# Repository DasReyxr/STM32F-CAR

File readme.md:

# Carrito Seguidor de Línea con Lógica Difusa

Este proyecto presenta un **carrito autónomo seguidor de línea** basado en un microcontrolador STM32 y un sistema de control por **lógica difusa (Fuzzy Logic)**. El objetivo es detectar la posición de la línea y ajustar la velocidad de los motores para mantener el seguimiento de manera estable y eficiente.

## ✨ Características principales
- Seguimiento automático de línea mediante sensores infrarrojos.
- Control adaptativo mediante lógica difusa.
- Implementación sobre plataforma STM32.
- Diseño orientado a demostración, pruebas y desarrollo académico.

## 🧠 ¿Cómo funciona?
El sistema lee la señal de los sensores, identifica si el carrito está ligeramente a la izquierda, a la derecha o sobre la línea, y genera una respuesta para corregir el movimiento de los motores, manteniéndose sobre la trayectoria.

## 🛠️ Diseño del sistema

El sistema sigue una secuencia clara de procesamiento:

1. **Adquisición de datos**: se toman las lecturas de los dos sensores.
2. **Difuminación de entradas**: los valores obtenidos se difuminan para representar el grado de pertenencia a las variables difusas.
3. **Reglas de Mamdani**: se aplican las reglas difusas para evaluar la acción de control.
4. **Defuzzificación por centroide**: se obtiene un valor numérico que indica la corrección necesaria.
5. **Actuación sobre los motores**: el resultado se envía al puente H para controlar el movimiento del carrito.

```mermaid
flowchart LR
    A[Sensor izquierdo] --> B[Lecturas de entrada]
    C[Sensor derecho] --> B
    B --> D[Difusificación]
    D --> E[Reglas de Mamdani]
    E --> F[Centroide]
    F --> G[Control de motores]
    G --> H[Motor izquierdo]
    G --> I[Motor derecho]
```

### Componentes principales
- **Microcontrolador:** BlackPill STM32F411CEU
- **Sensores:** QTR-8A
- **Puente H:** TB6612FNG
- **Control:** lógica difusa basada en reglas de Mamdani
- **Actuadores:** motores DC
- **Fuente de alimentación:** batería o fuente adecuada para el sistema

## 📷 Imagen del prototipo

A continuación se muestra una vista del prototipo desarrollado para el carrito seguidor de línea:

## 🎥 Demo
Aquí puedes ver una demostración del funcionamiento del carrito:

https://github.com/user-attachments/assets/0d9d8957-ae0a-4fae-b08e-12143651e8d6

## 👥 Equipo
- Roberto López - [Roberto](https://github.com/Roberto-dot)
- Kevin Lara - [Gyonyu](https://github.com/Gyonyu)
- Das Reyes - [Das](https://github.com/DasReyxr)

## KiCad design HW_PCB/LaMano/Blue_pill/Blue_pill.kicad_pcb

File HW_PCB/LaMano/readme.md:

# Log File
## 6-29-26

## 6-29-26

## 6-29-26

## 6-24-26

## 6-23-26

# 8-27-26

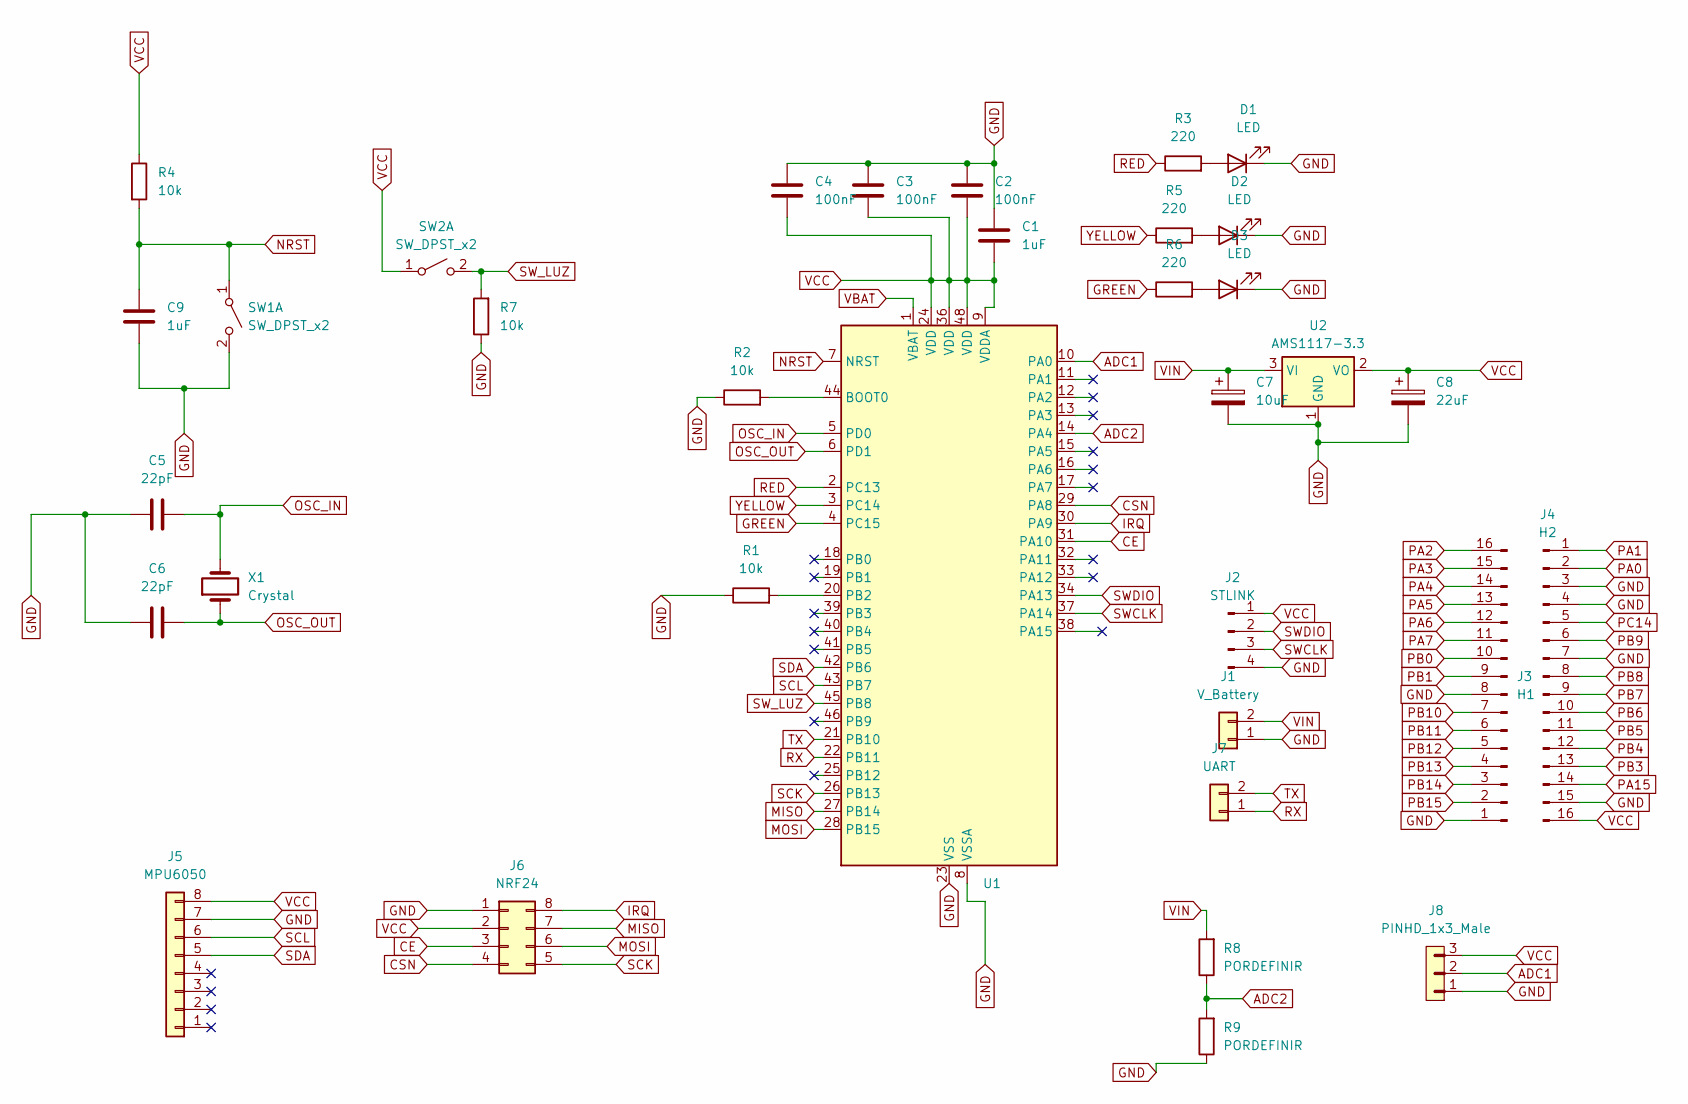
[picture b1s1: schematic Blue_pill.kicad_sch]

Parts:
C1, C9: 1uF; C_0805_2012Metric_Pad1.18x1.45mm_HandSolder
C2, C3, C4: 100nF; C_0805_2012Metric_Pad1.18x1.45mm_HandSolder
C5, C6: 22pF; C_0805_2012Metric_Pad1.18x1.45mm_HandSolder
C7: 10uF; C_0805_2012Metric_Pad1.18x1.45mm_HandSolder
C8: 22uF; C_0805_2012Metric_Pad1.18x1.45mm_HandSolder
D1, D2, D3: LED; LED_0805_2012Metric
J1: V_Battery; PinHeader_1x02_P2.54mm_Vertical
J2: STLINK; PinHeader_1x04_P2.54mm_Vertical
J3: H1; PinHeader_1x16_P2.54mm_Vertical
J4: H2; PinHeader_1x16_P2.54mm_Vertical
J5: MPU6050; PinHeader_1x08_P2.54mm_Vertical
J6: NRF24; PinHeader_2x04_P2.54mm_Vertical
J7: UART; PinHeader_1x02_P2.54mm_Vertical
J8: PINHD_1x3_Male; PinHeader_1x03_P2.54mm_Vertical
R1, R2, R4, R7: 10k; R_0805_2012Metric
R3, R5, R6: 220; R_0805_2012Metric
R8, R9: PORDEFINIR; R_0805_2012Metric
SW1: SW_DPST_x2; SWESPECIAL
SW2: SW_DPST_x2; PinHeader_1x02_P2.54mm_Vertical
U1: STM32F103C8Tx; LQFP-48_7x7mm_P0.5mm
U2: AMS1117-3.3; SOT-223-3_TabPin2
X1: Crystal; XTAL_NX5032GA-8.000M-STD-CSU-1

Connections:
ADC1: J8.2, U1.10 (PA0)
ADC2: R8.1, R9.2, U1.14 (PA4)
CE: J6.3, U1.31 (PA10)
CSN: J6.4, U1.29 (PA8)
GND: C1.2, C2.2, C3.2, C4.2, C5.2, C6.2, C7.2, C8.2, C9.1, D1.1 (K), D2.1 (K), D3.1 (K), J1.1, J2.4, J3.1, J3.8, J4.3, J4.4, J4.7, J4.15, J5.7, J6.1, J8.1, R1.1, R2.1, R7.1, R9.1, SW1.2 (B), U1.8 (VSSA), U1.23 (VSS), U1.35 (VSS), U1.47 (VSS), U2.1 (GND)
GREEN: R6.1, U1.4 (PC15)
IRQ: J6.8, U1.30 (PA9)
MISO: J6.7, U1.27 (PB14)
MOSI: J6.6, U1.28 (PB15)
NRST: C9.2, R4.2, SW1.1 (A), U1.7 (NRST)
unnamed: D1.2 (A), R3.2
unnamed: D2.2 (A), R5.2
unnamed: D3.2 (A), R6.2
unnamed: R2.2, U1.44 (BOOT0)
unnamed: R1.2, U1.20 (PB2)
OSC_IN: C5.1, U1.5 (PD0), X1.2
OSC_OUT: C6.1, U1.6 (PD1), X1.1
RED: R3.1, U1.2 (PC13)
RX: J7.1, U1.22 (PB11)
SCK: J6.5, U1.26 (PB13)
SCL: J5.6, U1.43 (PB7)
SDA: J5.5, U1.42 (PB6)
SWCLK: J2.3, U1.37 (PA14)
SWDIO: J2.2, U1.34 (PA13)
SW_LUZ: R7.2, SW2.2 (B), U1.45 (PB8)
TX: J7.2, U1.21 (PB10)
VBAT: U1.1 (VBAT)
VCC: C1.1, C2.1, C3.1, C4.1, C8.1, J2.1, J4.16, J5.8, J6.2, J8.3, R4.1, SW2.1 (A), U1.9 (VDDA), U1.24 (VDD), U1.36 (VDD), U1.48 (VDD), U2.2 (VO)
VIN: C7.1, J1.2, R8.2, U2.3 (VI)
YELLOW: R5.1, U1.3 (PC14)

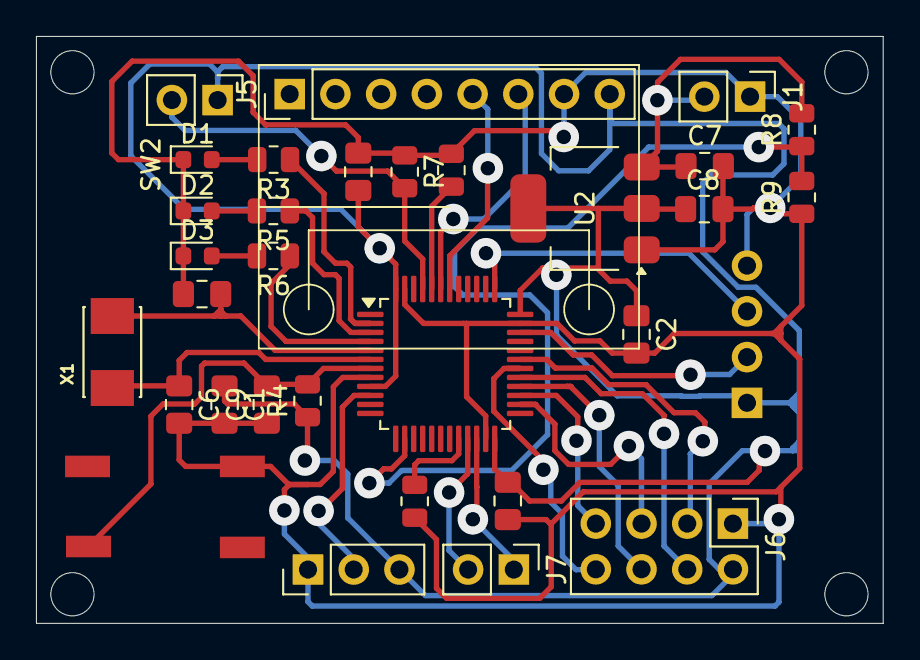
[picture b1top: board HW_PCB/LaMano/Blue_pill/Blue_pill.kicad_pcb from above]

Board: 2 copper layers, 47.0 x 32.6 mm, 32 parts (1 on the bottom side), 29 nets.

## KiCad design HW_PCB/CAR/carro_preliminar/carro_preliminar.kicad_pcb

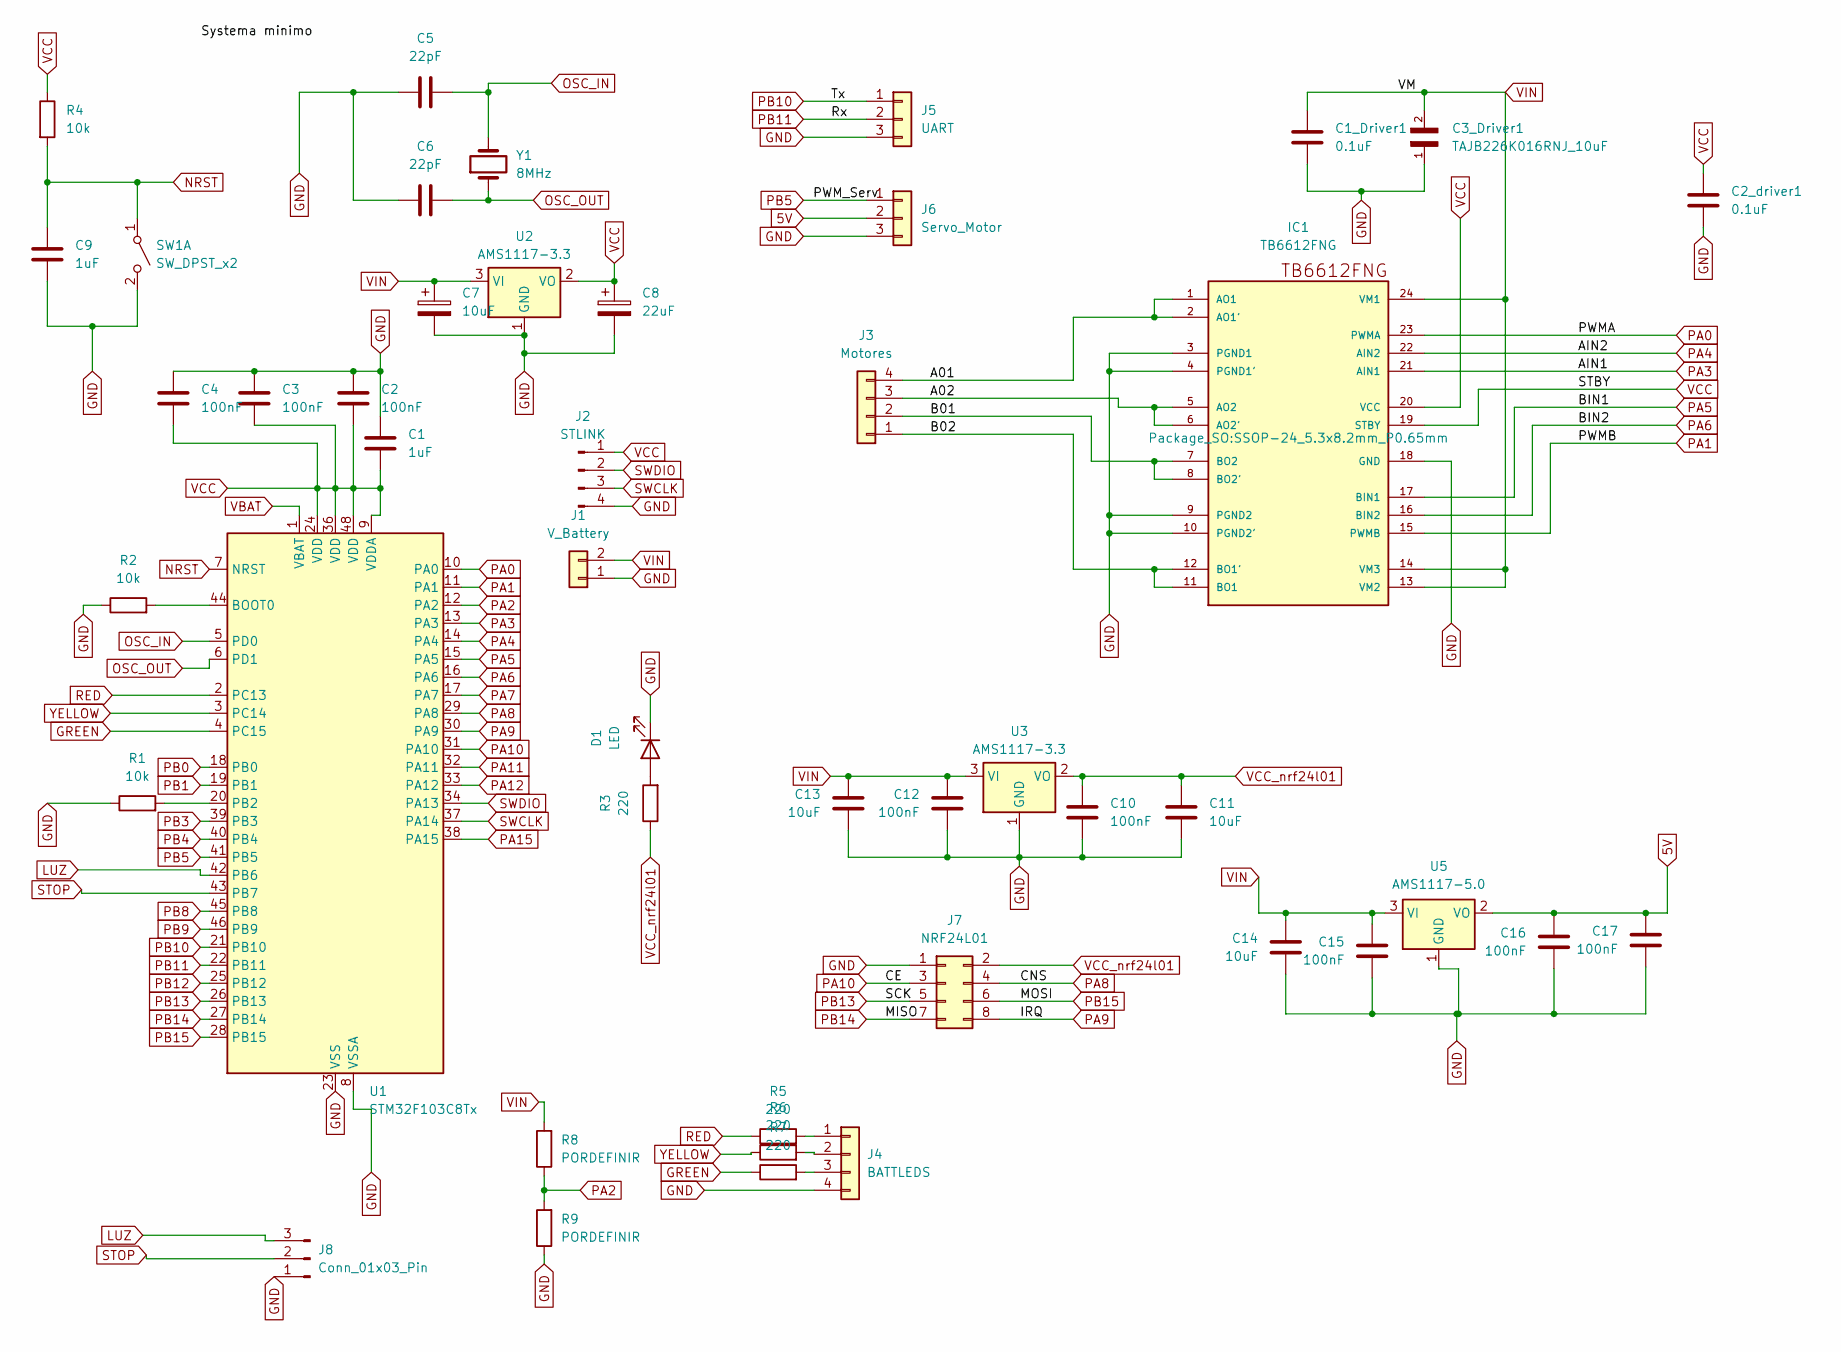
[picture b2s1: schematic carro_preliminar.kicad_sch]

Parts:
C1: 1uF; C_0805_2012Metric
C1_Driver1, C2_driver1: 0.1uF; C_0805_2012Metric
C2, C3, C4, C10, C12, C15, C16, C17: 100nF; C_0805_2012Metric_Pad1.18x1.45mm_HandSolder
C3_Driver1: TAJB226K016RNJ_10uF; CAPPC3528X210N; DigiKey_Part_Number 478-1682-1-ND
C5, C6: 22pF; C_0805_2012Metric_Pad1.18x1.45mm_HandSolder
C7, C11, C13, C14: 10uF; C_0805_2012Metric_Pad1.18x1.45mm_HandSolder
C8: 22uF; C_0805_2012Metric_Pad1.18x1.45mm_HandSolder
C9: 1uF; C_0805_2012Metric_Pad1.18x1.45mm_HandSolder
D1: LED; LED_0603_1608Metric
IC1: TB6612FNG; SSOP-24_5.3x8.2mm_P0.65mm
J1: V_Battery; PinHeader_1x02_P2.54mm_Vertical
J2: STLINK; PinHeader_1x04_P2.54mm_Vertical
J3: Motores; PinHeader_1x04_P2.54mm_Vertical
J4: BATTLEDS; PinHeader_1x04_P2.54mm_Vertical
J5: UART; PinHeader_1x03_P2.54mm_Vertical
J6: Servo_Motor; PinHeader_1x03_P2.54mm_Vertical
J7: NRF24L01; PinHeader_2x04_P2.54mm_Vertical
J8: Conn_01x03_Pin; PinHeader_1x03_P2.54mm_Vertical
R1, R2, R4: 10k; R_0805_2012Metric
R3, R5, R6, R7: 220; R_0805_2012Metric
R8, R9: PORDEFINIR; R_0805_2012Metric
SW1: SW_DPST_x2; Untitled
U1: STM32F103C8Tx; LQFP-48_7x7mm_P0.5mm
U2, U3: AMS1117-3.3; SOT-223-3_TabPin2
U5: AMS1117-5.0; SOT-223-3_TabPin2
Y1: 8MHz; XTAL_NX5032GA-8.000M-STD-CSU-1

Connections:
5V: C16.1, C17.1, J6.2, U5.2 (VO)
/A01: IC1.1 (AO1), IC1.2 (AO1'), J3.4
/A02: IC1.5 (AO2), IC1.6 (AO2'), J3.3
/B01: IC1.7 (BO2), IC1.8 (BO2'), J3.2
/B02: IC1.11 (BO1), IC1.12 (BO1'), J3.1
GND: C1.2, C1_Driver1.2, C2.2, C2_driver1.2, C3.2, C3_Driver1.1, C4.2, C5.2, C6.2, C7.2, C8.2, C9.1, C10.2, C11.2, C12.2, C13.2, C14.2, C15.2, C16.2, C17.2, D1.1 (K), IC1.3 (PGND1), IC1.4 (PGND1'), IC1.9 (PGND2), IC1.10 (PGND2'), IC1.18 (GND), J1.1, J2.4, J4.4, J5.3, J6.3, J7.1, J8.1, R1.1, R2.1, R9.1, SW1.2 (B), U1.8 (VSSA), U1.23 (VSS), U1.35 (VSS), U1.47 (VSS), U2.1 (GND), U3.1 (GND), U5.1 (GND)
GREEN: R7.1, U1.4 (PC15)
LUZ: J8.3, U1.42 (PB6)
NRST: C9.2, R4.2, SW1.1 (A), U1.7 (NRST)
unnamed: D1.2 (A), R3.2
unnamed: J4.1, R5.2
unnamed: J4.2, R6.2
unnamed: J4.3, R7.2
unnamed: R2.2, U1.44 (BOOT0)
unnamed: R1.2, U1.20 (PB2)
OSC_IN: C5.1, U1.5 (PD0), Y1.2
OSC_OUT: C6.1, U1.6 (PD1), Y1.1
PA0: IC1.23 (PWMA), U1.10 (PA0)
PA1: IC1.15 (PWMB), U1.11 (PA1)
PA2: R8.1, R9.2, U1.12 (PA2)
PA3: IC1.21 (AIN1), U1.13 (PA3)
PA4: IC1.22 (AIN2), U1.14 (PA4)
PA5: IC1.17 (BIN1), U1.15 (PA5)
PA6: IC1.16 (BIN2), U1.16 (PA6)
PA7: U1.17 (PA7)
PA8: J7.4, U1.29 (PA8)
PA9: J7.8, U1.30 (PA9)
PA10: J7.3, U1.31 (PA10)
PA11: U1.32 (PA11)
PA12: U1.33 (PA12)
PA15: U1.38 (PA15)
PB0: U1.18 (PB0)
PB1: U1.19 (PB1)
PB3: U1.39 (PB3)
PB4: U1.40 (PB4)
PB5: J6.1, U1.41 (PB5)
PB8: U1.45 (PB8)
PB9: U1.46 (PB9)
PB10: J5.1, U1.21 (PB10)
PB11: J5.2, U1.22 (PB11)
PB12: U1.25 (PB12)
PB13: J7.5, U1.26 (PB13)
PB14: J7.7, U1.27 (PB14)
PB15: J7.6, U1.28 (PB15)
RED: R5.1, U1.2 (PC13)
STOP: J8.2, U1.43 (PB7)
SWCLK: J2.3, U1.37 (PA14)
SWDIO: J2.2, U1.34 (PA13)
VBAT: U1.1 (VBAT)
VCC: C1.1, C2.1, C2_driver1.1, C3.1, C4.1, C8.1, IC1.19 (STBY), IC1.20 (VCC), J2.1, R4.1, U1.9 (VDDA), U1.24 (VDD), U1.36 (VDD), U1.48 (VDD), U2.2 (VO)
VCC_nrf24l01: C10.1, C11.1, J7.2, R3.1, U3.2 (VO)
VIN: C1_Driver1.1, C3_Driver1.2, C7.1, C12.1, C13.1, C14.1, C15.1, IC1.13 (VM2), IC1.14 (VM3), IC1.24 (VM1), J1.2, R8.2, U2.3 (VI), U3.3 (VI), U5.3 (VI)
YELLOW: R6.1, U1.3 (PC14)

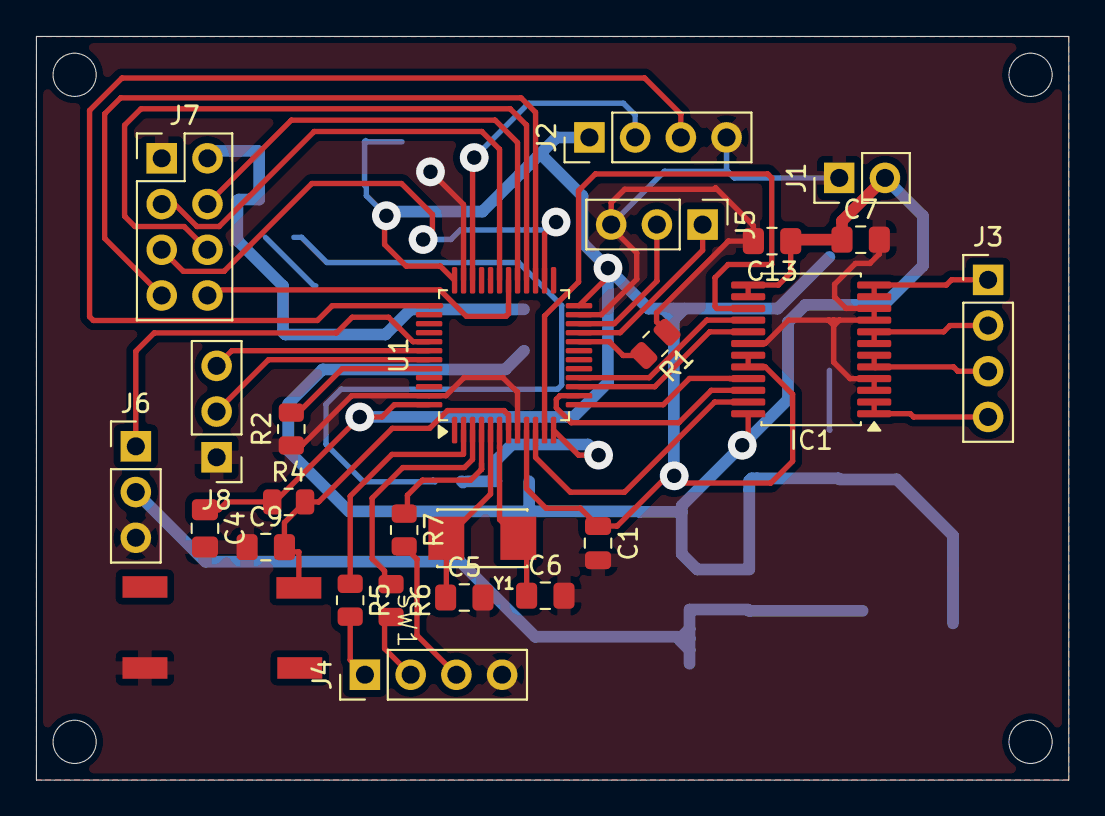
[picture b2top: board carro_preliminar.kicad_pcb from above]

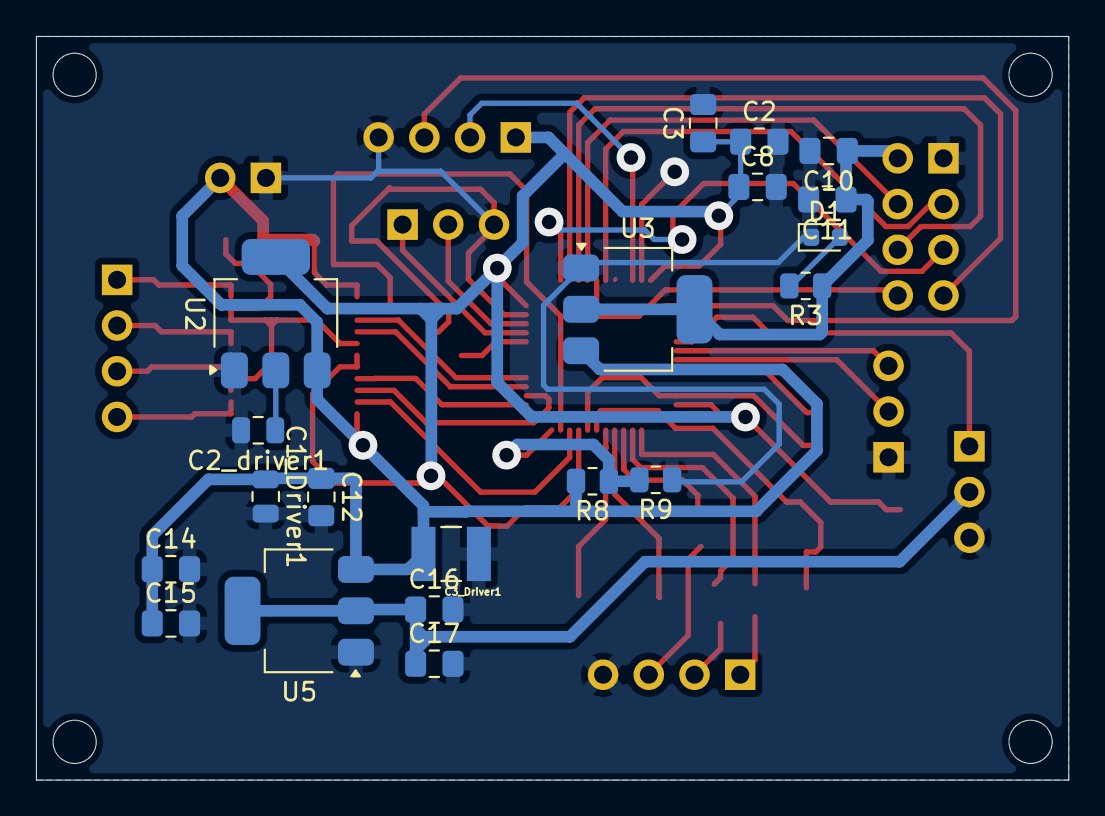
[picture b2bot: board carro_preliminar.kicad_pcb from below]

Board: 2 copper layers, 57.4 x 41.3 mm, 45 parts (20 on the bottom side), 41 nets.

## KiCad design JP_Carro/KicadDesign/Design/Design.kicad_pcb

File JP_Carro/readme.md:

# Carrito Seguidor de Línea con Lógica Difusa

Este proyecto presenta un **carrito autónomo seguidor de línea** basado en un microcontrolador STM32 y un sistema de control por **lógica difusa (Fuzzy Logic)**. El objetivo es detectar la posición de la línea y ajustar la velocidad de los motores para mantener el seguimiento de forma estable y eficiente.

## ✨ Características principales
- Seguimiento automático de línea mediante sensores infrarrojos.
- Control adaptativo usando lógica difusa.
- Implementación sobre plataforma STM32.
- Diseño orientado a demostración, pruebas y desarrollo académico.

## 🧠 ¿Cómo funciona?
El sistema lee la señal de los sensores, identifica si el robot está ligeramente a la izquierda, derecha o sobre la línea, y genera una respuesta para corregir el movimiento de los motores.

## 🛠️ Diseño del sistema

El sistema se basa en una secuencia clara de procesamiento:

1. **Adquisición de datos**: se toman las lecturas de los dos sensores.
2. **Difusión de entradas**: los valores obtenidos se difuminan para representar el grado de pertenencia a las variables difusas.
3. **Reglas de Mamdani**: se aplican las reglas difusas para evaluar la acción de control.
4. **Defuzzificación por centroide**: se obtiene un valor numérico que indica la corrección necesaria.
5. **Actuación sobre los motores**: el resultado se envía al puente H para controlar el movimiento del carrito.

```mermaid
flowchart LR
    A[Sensor izquierdo] --> B[Lecturas de entrada]
    C[Sensor derecho] --> B
    B --> D[Difusificación]
    D --> E[Reglas de Mamdani]
    E --> F[Centroide]
    F --> G[Control de motores]
    G --> H[Motor izquierdo]
    G --> I[Motor derecho]
```

### Componentes principales
- **Microcontrolador:** BlackPill STM32F411CEU
- **Sensores:** QTR-8A
- **Puente H:** TB6612FNG
- **Control:** lógica difusa basada en reglas de Mamdani
- **Actuadores:** motores DC
- **Fuente de alimentación:** batería o fuente adecuada para el sistema

## 📷 Imagen del prototipo

A continuación se muestra una vista del prototipo desarrollado para el carrito seguidor de línea:

## 🎥 Demo
Aquí puedes ver una demostración del funcionamiento del carrito:

https://github.com/user-attachments/assets/0d9d8957-ae0a-4fae-b08e-12143651e8d6

## 👥 Equipo
- Roberto López - [Roberto](https://github.com/Roberto-dot)
- Kevin Lara - [Gyonyu](https://github.com/Gyonyu)
- Das Reyes - [Das](https://github.com/DasReyxr)

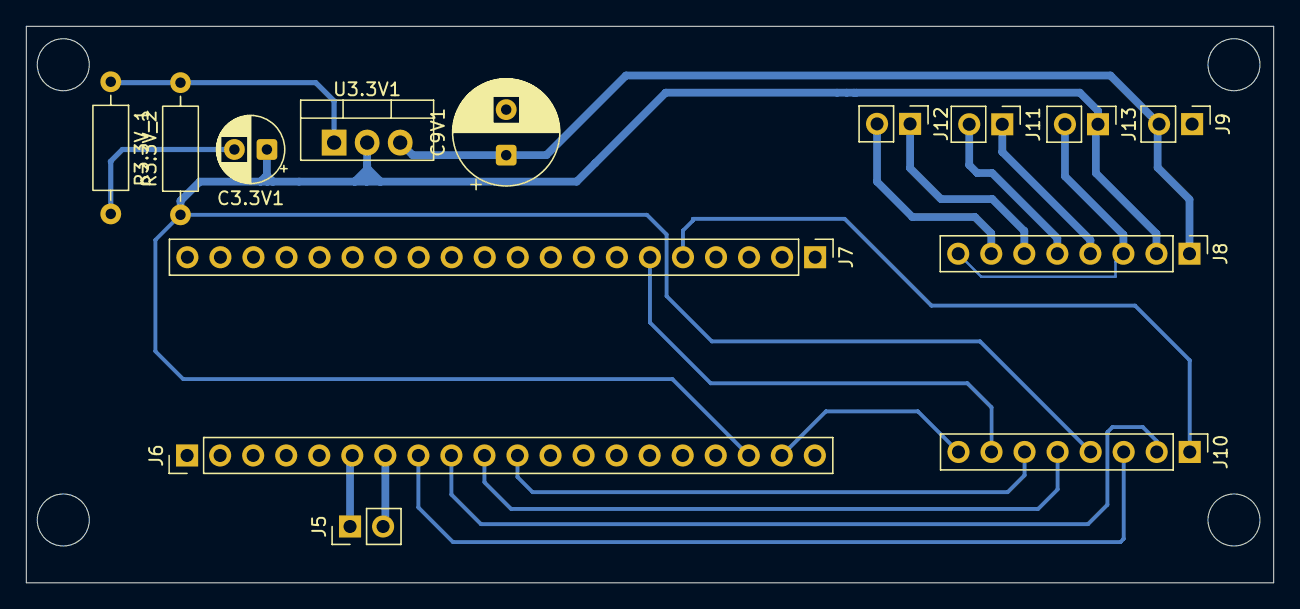
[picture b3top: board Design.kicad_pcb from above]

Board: 2 copper layers, 95.9 x 42.8 mm, 14 parts (0 on the bottom side), 16 nets.

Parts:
C3.3V1: 100uF; CP_Radial_D5.0mm_P2.50mm
C9V1: 100uF; CP_Radial_D8.0mm_P3.50mm
J5: SENSOR; PinHeader_1x02_P2.54mm_Vertical
J6, J7: Conn_01x20_Socket; PinHeader_1x20_P2.54mm_Vertical
J8: Puente H; PinHeader_1x08_P2.54mm_Vertical
J9: 9V; PinHeader_1x02_P2.54mm_Vertical
J10: Puente_H2; PinHeader_1x08_P2.54mm_Vertical
J11: A MOTOR; PinHeader_1x02_P2.54mm_Vertical
J12: B MOTOR; PinHeader_1x02_P2.54mm_Vertical
J13: SENSOR_SOURCE; PinHeader_1x02_P2.54mm_Vertical
R3.3V_1: 1500; R_Axial_DIN0207_L6.3mm_D2.5mm_P10.16mm_Horizontal
R3.3V_2: 1K; R_Axial_DIN0207_L6.3mm_D2.5mm_P10.16mm_Horizontal
U3.3V1: LM317_TO-220; TO-220-3_Vertical

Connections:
3.3V: C3.3V1.1, J6.18, J8.2, J10.4, J13.1, R3.3V_2.1, U3.3V1.2 (VO)
9V: C9V1.1, J8.1, J9.2, U3.3V1.3 (VI)
/A01: J8.4, J11.1
/A02: J8.5, J11.2
/B01: J8.6, J12.1
/B02: J8.7, J12.2
A0 ADC_1: J5.1, J6.6
A1 ADC_2: J5.2, J6.7
A2 AIN1: J6.8, J10.3
A3 AIN2: J6.9, J10.2
A4 BIN1: J6.10, J10.5
A5 BIN2: J6.11, J10.6
A8 PWM_IZQ: J7.5, J10.1
A9 PWM_DER: J7.6, J10.7
GND: C3.3V1.2, C9V1.2, J6.19, J8.3, J8.8, J9.1, J10.8, J13.2, R3.3V_1.2
unnamed: R3.3V_1.1, R3.3V_2.2, U3.3V1.1 (ADJ)

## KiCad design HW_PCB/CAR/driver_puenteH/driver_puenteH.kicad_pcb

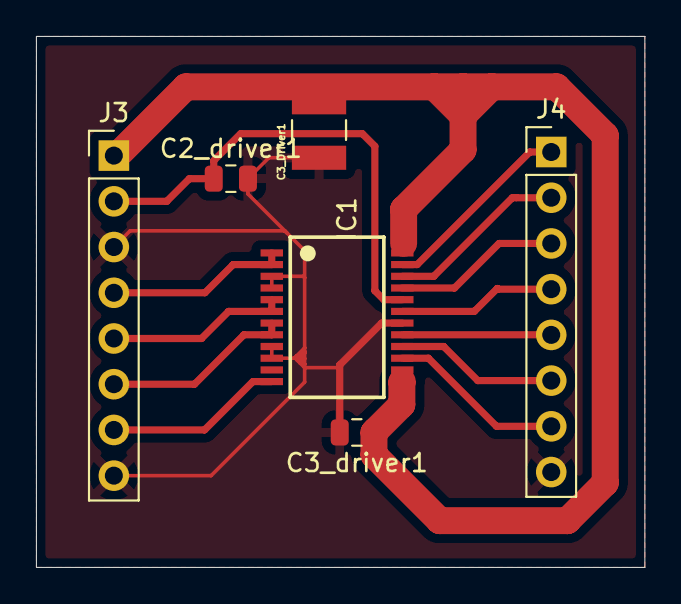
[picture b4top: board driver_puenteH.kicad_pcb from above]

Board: 2 copper layers, 33.8 x 29.5 mm, 6 parts (0 on the bottom side), 14 nets.

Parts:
C2_driver1: 0.1uF; C_0805_2012Metric
C3_Driver1: TAJB226K016RNJ_10uF; CAPPC3528X210N
C3_driver1: 10uF; C_0805_2012Metric
IC1: TB6612FNG; SSOP24
J3: Puente H; PinHeader_1x08_P2.54mm_Vertical
J4: Puente_H2; PinHeader_1x08_P2.54mm_Vertical

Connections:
/A01: IC1.1 (AO1), IC1.2 (AO1'), J3.4
/A02: IC1.5 (AO2), IC1.6 (AO2'), J3.5
/AIN1: IC1.21 (AIN1), J4.3
/AIN2: IC1.22 (AIN2), J4.2
/B01: IC1.7 (BO2), IC1.8 (BO2'), J3.6
/B02: IC1.11 (BO1), IC1.12 (BO1'), J3.7
/BIN1: IC1.17 (BIN1), J4.5
/BIN2: IC1.16 (BIN2), J4.6
/PWMA: IC1.23 (PWMA), J4.1
/PWMB: IC1.15 (PWMB), J4.7
/STBY: IC1.19 (STBY), J4.4
/VM: C3_Driver1.2, C3_driver1.1, IC1.13 (VM2), IC1.14 (VM3), IC1.24 (VM1), J3.1
GND: C2_driver1.2, C3_Driver1.1, C3_driver1.2, IC1.3 (PGND1), IC1.4 (PGND1'), IC1.9 (PGND2), IC1.10 (PGND2'), IC1.18 (GND), J3.3, J3.8, J4.8
VCC: C2_driver1.1, IC1.20 (VCC), J3.2

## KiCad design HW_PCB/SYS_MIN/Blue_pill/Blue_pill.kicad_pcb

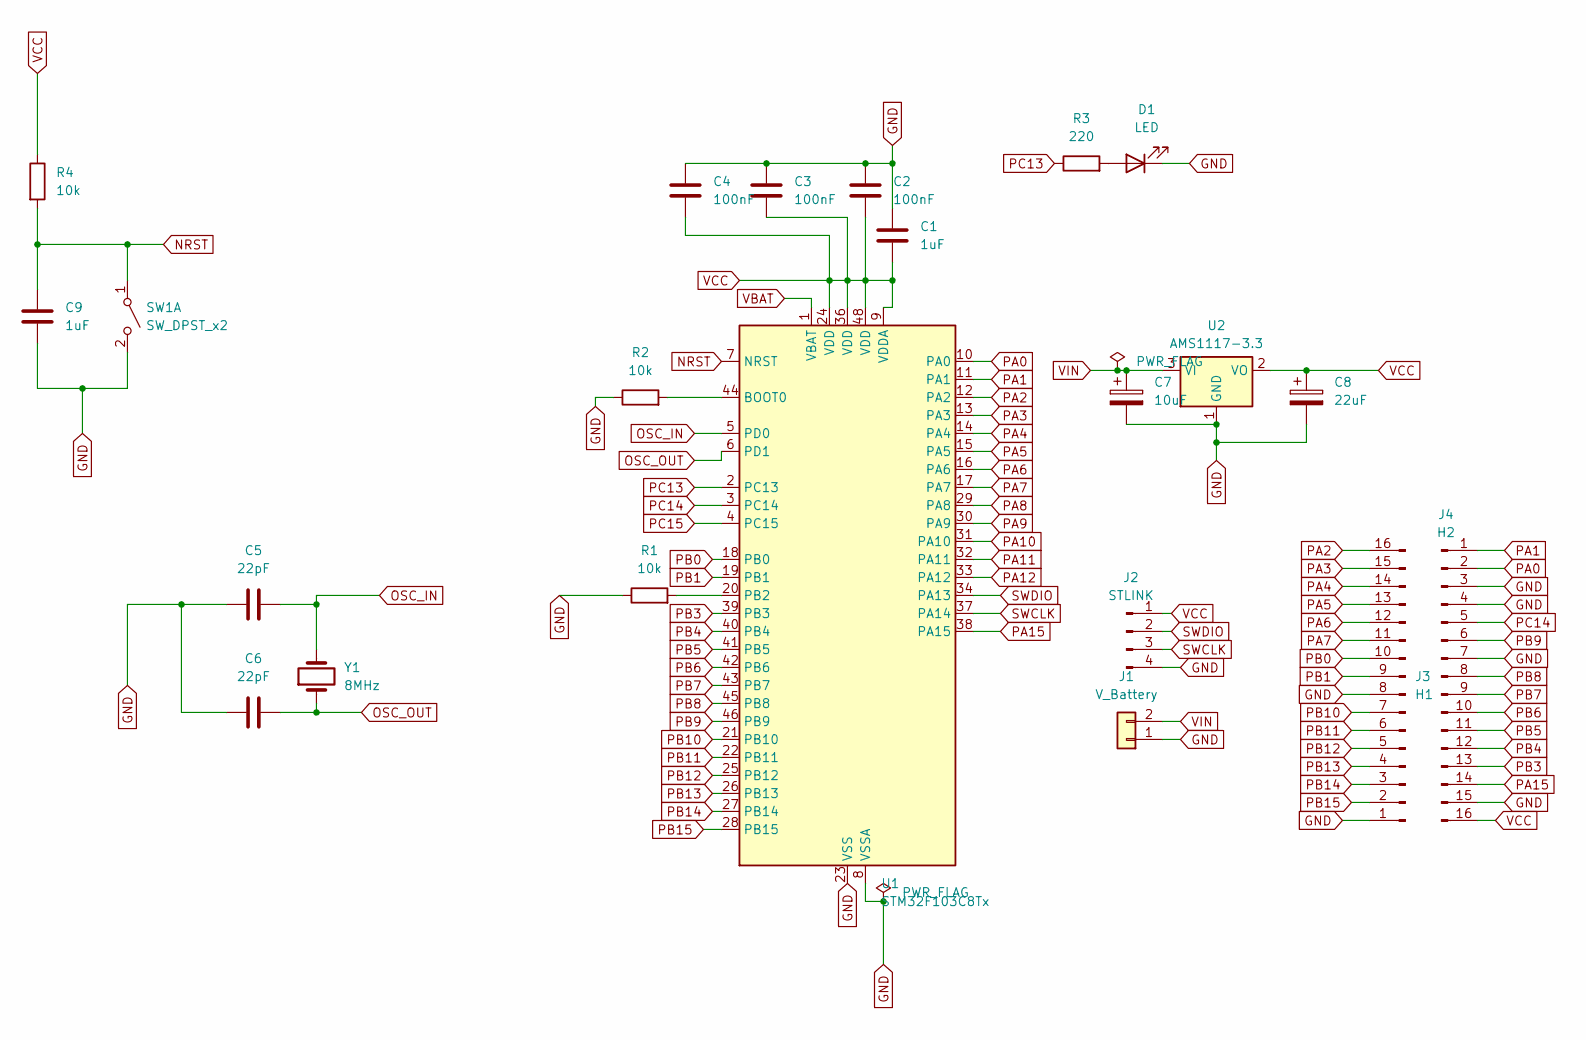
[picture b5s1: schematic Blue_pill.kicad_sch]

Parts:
C1: 1uF; C_0805_2012Metric
C2, C3, C4: 100nF; C_0805_2012Metric_Pad1.18x1.45mm_HandSolder
C5, C6: 22pF; C_0805_2012Metric_Pad1.18x1.45mm_HandSolder
C7: 10uF; C_0805_2012Metric_Pad1.18x1.45mm_HandSolder
C8: 22uF; C_0805_2012Metric_Pad1.18x1.45mm_HandSolder
C9: 1uF; C_0805_2012Metric_Pad1.18x1.45mm_HandSolder
D1: LED; LED_0603_1608Metric
J1: V_Battery; PinHeader_1x02_P2.54mm_Vertical
J2: STLINK; PinHeader_1x04_P2.54mm_Vertical
J3: H1; PinHeader_1x16_P2.54mm_Vertical
J4: H2; PinHeader_1x16_P2.54mm_Vertical
R1, R2, R4: 10k; R_0805_2012Metric
R3: 220; R_0805_2012Metric
SW1: SW_DPST_x2; Untitled
U1: STM32F103C8Tx; LQFP-48_7x7mm_P0.5mm
U2: AMS1117-3.3; SOT-223-3_TabPin2
Y1: 8MHz; Crystal_SMD_EuroQuartz_MQ2-2Pin_7.0x5.0mm

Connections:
GND: C1.2, C2.2, C3.2, C4.2, C5.2, C6.2, C7.2, C8.2, C9.1, D1.1 (K), J1.1, J2.4, J3.1, J3.8, J4.3, J4.4, J4.7, J4.15, R1.1, R2.1, SW1.2 (B), U1.8 (VSSA), U1.23 (VSS), U1.35 (VSS), U1.47 (VSS), U2.1 (GND)
NRST: C9.2, R4.2, SW1.1 (A), U1.7 (NRST)
unnamed: D1.2 (A), R3.2
unnamed: R2.2, U1.44 (BOOT0)
unnamed: R1.2, U1.20 (PB2)
OSC_IN: C5.1, U1.5 (PD0), Y1.2
OSC_OUT: C6.1, U1.6 (PD1), Y1.1
PA0: J4.2, U1.10 (PA0)
PA1: J4.1, U1.11 (PA1)
PA2: J3.16, U1.12 (PA2)
PA3: J3.15, U1.13 (PA3)
PA4: J3.14, U1.14 (PA4)
PA5: J3.13, U1.15 (PA5)
PA6: J3.12, U1.16 (PA6)
PA7: J3.11, U1.17 (PA7)
PA8: U1.29 (PA8)
PA9: U1.30 (PA9)
PA10: U1.31 (PA10)
PA11: U1.32 (PA11)
PA12: U1.33 (PA12)
PA15: J4.14, U1.38 (PA15)
PB0: J3.10, U1.18 (PB0)
PB1: J3.9, U1.19 (PB1)
PB3: J4.13, U1.39 (PB3)
PB4: J4.12, U1.40 (PB4)
PB5: J4.11, U1.41 (PB5)
PB6: J4.10, U1.42 (PB6)
PB7: J4.9, U1.43 (PB7)
PB8: J4.8, U1.45 (PB8)
PB9: J4.6, U1.46 (PB9)
PB10: J3.7, U1.21 (PB10)
PB11: J3.6, U1.22 (PB11)
PB12: J3.5, U1.25 (PB12)
PB13: J3.4, U1.26 (PB13)
PB14: J3.3, U1.27 (PB14)
PB15: J3.2, U1.28 (PB15)
PC13: R3.1, U1.2 (PC13)
PC14: J4.5, U1.3 (PC14)
PC15: U1.4 (PC15)
SWCLK: J2.3, U1.37 (PA14)
SWDIO: J2.2, U1.34 (PA13)
VBAT: U1.1 (VBAT)
VCC: C1.1, C2.1, C3.1, C4.1, C8.1, J2.1, J4.16, R4.1, U1.9 (VDDA), U1.24 (VDD), U1.36 (VDD), U1.48 (VDD), U2.2 (VO)
VIN: C7.1, J1.2, U2.3 (VI)

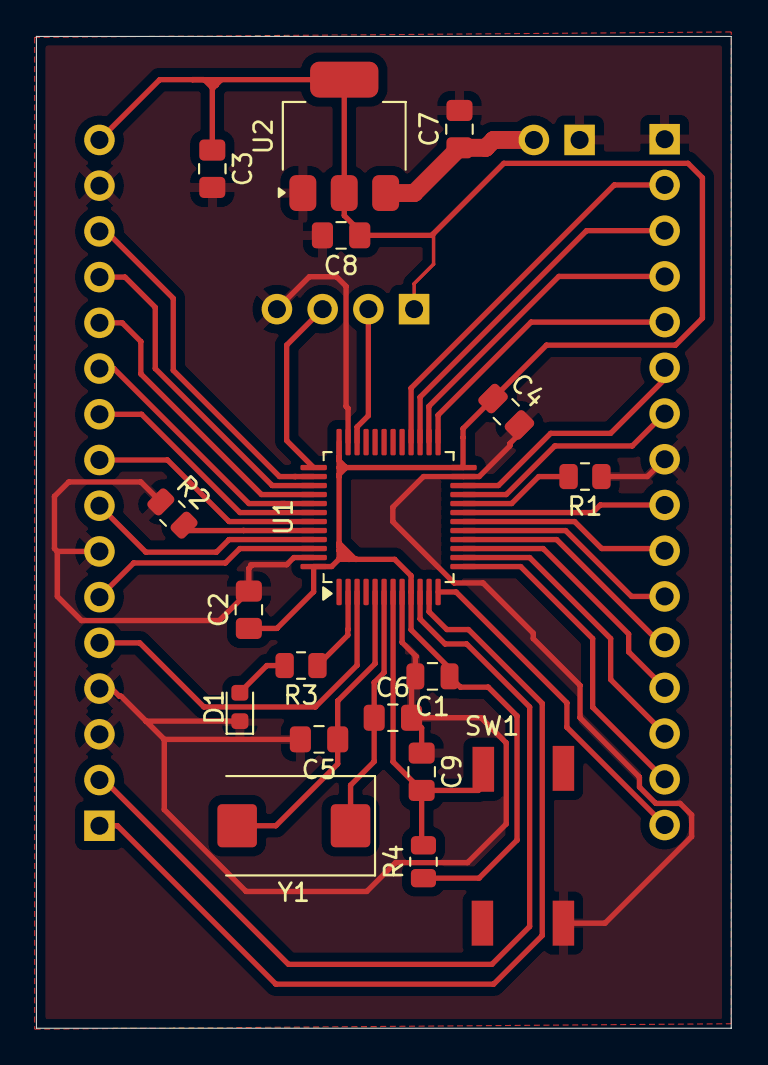
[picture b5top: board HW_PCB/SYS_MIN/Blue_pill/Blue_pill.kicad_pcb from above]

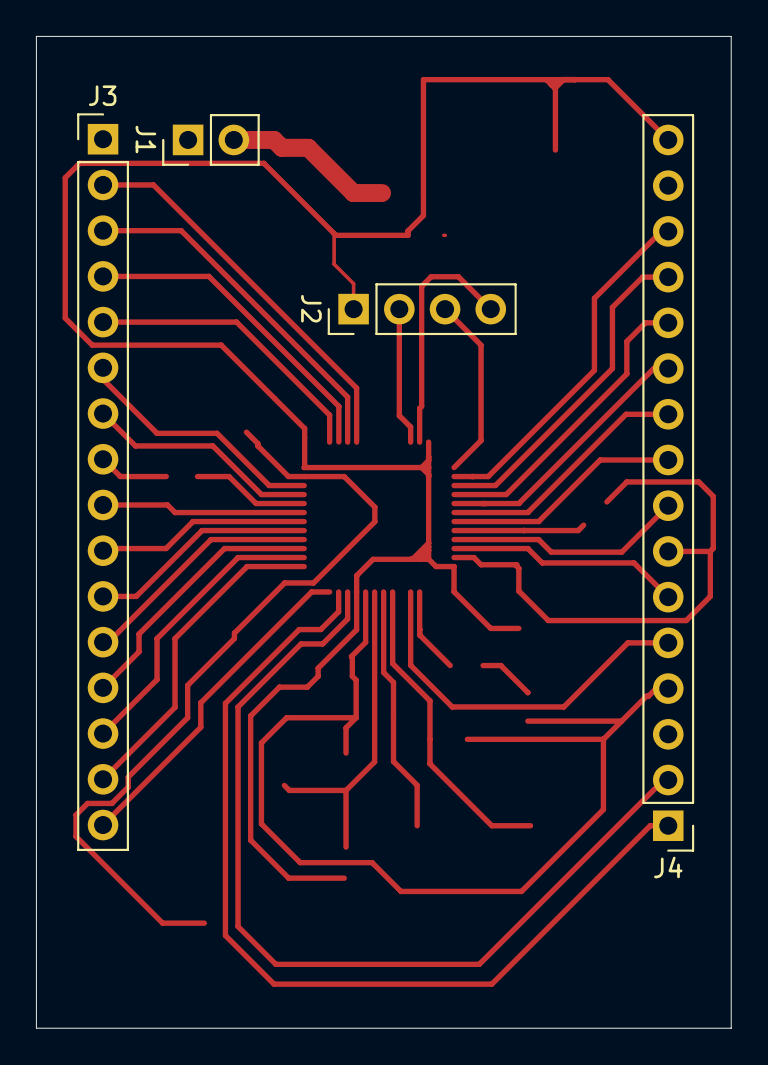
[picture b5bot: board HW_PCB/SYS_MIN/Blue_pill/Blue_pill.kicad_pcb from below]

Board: 2 copper layers, 38.6 x 55.1 mm, 22 parts (4 on the bottom side), 37 nets.

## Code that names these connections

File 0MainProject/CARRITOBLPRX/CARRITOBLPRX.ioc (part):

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Mcu.Name=STM32F103C(8-B)Tx
Mcu.Package=LQFP48
Mcu.UserName=STM32F103C8Tx
PA0-WKUP.Signal=S_TIM2_CH1_ETR
PA1.Signal=S_TIM2_CH2
PA10.GPIOParameters=GPIO_Speed,GPIO_Label
PA10.GPIO_Label=CE
PA10.GPIO_Speed=GPIO_SPEED_FREQ_HIGH
PA10.Signal=GPIO_Output
PA13.Mode=Serial_Wire
PA13.Signal=SYS_JTMS-SWDIO
PA14.Mode=Serial_Wire
PA14.Signal=SYS_JTCK-SWCLK
PA2.Signal=ADCx_IN2
PA3.GPIOParameters=GPIO_Speed,GPIO_Label
PA3.GPIO_Label=LeftFront
PA3.GPIO_Speed=GPIO_SPEED_FREQ_HIGH
PA3.Signal=GPIO_Output
PA4.GPIOParameters=GPIO_Speed,GPIO_Label
PA4.GPIO_Label=LeftBack
PA4.GPIO_Speed=GPIO_SPEED_FREQ_HIGH
PA4.Signal=GPIO_Output
PA5.GPIOParameters=GPIO_Speed,GPIO_Label
PA5.GPIO_Label=RightFront
PA5.GPIO_Speed=GPIO_SPEED_FREQ_HIGH
PA5.Signal=GPIO_Output
PA6.GPIOParameters=GPIO_Speed,GPIO_Label
PA6.GPIO_Label=RightBack
PA6.GPIO_Speed=GPIO_SPEED_FREQ_HIGH
PA6.Signal=GPIO_Output
PA8.GPIOParameters=GPIO_Speed,GPIO_Label
PA8.GPIO_Label=CSN
PA8.GPIO_Speed=GPIO_SPEED_FREQ_HIGH
PA8.Signal=GPIO_Output
PA9.GPIOParameters=GPIO_Label,GPIO_ModeDefaultEXTI
PA9.GPIO_Label=IRQ
PA9.GPIO_ModeDefaultEXTI=GPIO_MODE_IT_FALLING
PA9.Signal=GPXTI9
PB0.GPIOParameters=GPIO_Label
PB0.GPIO_Label=LED_DIR1
PB0.Signal=GPIO_Output
PB1.GPIOParameters=GPIO_Label
PB1.GPIO_Label=LED_DIR2
PB1.Signal=GPIO_Output
PB10.Mode=Asynchronous
PB10.Signal=USART3_TX
PB11.Mode=Asynchronous
PB11.Signal=USART3_RX
PB13.Mode=Full_Duplex_Master
PB13.Signal=SPI2_SCK
PB14.Mode=Full_Duplex_Master
PB14.Signal=SPI2_MISO
PB15.Mode=Full_Duplex_Master
PB15.Signal=SPI2_MOSI
PB5.Signal=S_TIM3_CH2
PB6.GPIOParameters=GPIO_Label
PB6.GPIO_Label=LUZ
PB6.Signal=GPIO_Output
PB7.GPIOParameters=GPIO_Label
PB7.GPIO_Label=STOP
PB7.Signal=GPIO_Output
PC13-TAMPER-RTC.GPIOParameters=GPIO_Label
PC13-TAMPER-RTC.GPIO_Label=RED
PC13-TAMPER-RTC.Signal=GPIO_Output
PC14-OSC32_IN.GPIOParameters=GPIO_Label
PC14-OSC32_IN.GPIO_Label=YELLOW
PC14-OSC32_IN.Signal=GPIO_Output
PC15-OSC32_OUT.GPIOParameters=GPIO_Label
PC15-OSC32_OUT.GPIO_Label=GREEN
PC15-OSC32_OUT.Signal=GPIO_Output
PD0-OSC_IN.Mode=HSE-External-Oscillator
PD0-OSC_IN.Signal=RCC_OSC_IN
PD1-OSC_OUT.Mode=HSE-External-Oscillator
PD1-OSC_OUT.Signal=RCC_OSC_OUT
RCC.SYSCLKFreq_VALUE=16000000
RCC.SYSCLKSource=RCC_SYSCLKSOURCE_PLLCLK
board=custom

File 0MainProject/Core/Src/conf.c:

#include "conf.h"

/*
PINOUT
M1 Left
M2 Right

A Peripherals

PA0 PWM2Ch1
PA1 PWM2Ch2


PA3 M1 Front
PA4 M1 Back

PA5 M2 Front
PA6 M2 Back

PB0 LEDs Left
PB1 LEDs Right

PB5 PWM SERVOMOTOR TIMER3

PB12 CSN
PB11 IRQ
PB10 CE

PB[13:15] SPI
PB13 SCK
PB14 MISO
PB15 MOSI

*/
#define LeftFront 3
#define LeftBack 4
#define RightFront 5
#define RightBack 6
#define PI	3.14159265358979

// Definir buzer y nrf




/*--- Clase Carro ----*/

    /*
    Valor minimo 200 -45
    Valor maximo 280 +45
    TIM3 servo motor direccion
    TIM2 mmo
    */


void CAR_Leds(void){
    GPIOB->ODR &= ~(3<<0);
    // Checar si es menor que 235
    if(TIM3->CCR1>115)
        GPIOB->ODR |= (1<<0);
    // Checar si es menor que 245
    if(TIM3->CCR1 < 125)
        GPIOB->ODR |= (1<<1);

}


/* Motor Functions */
void CAR_Speed(uint16_t speed){
    if(speed>100)speed=100;
    TIM2->CCR1= (65535*speed)/100; //DUTYCYCLE 50% CHANEL1
    TIM2->CCR2= (65535*speed)/100; //DUTYCYCLE 50% CHANEL2
}


void CAR_Front(void){
    GPIOA->ODR &=(0<<RightBack)|(0<<LeftBack);
    GPIOA->ODR |=(1<<RightFront)|(1<<LeftFront);
}
void CAR_Back(void){
    GPIOA->ODR &=(0<<RightFront)|(0<<LeftFront);
    GPIOA->ODR |=(1<<RightBack)|(1<<LeftBack);
}

void CAR_Direction(float angle){//HAY QUE LIMITAR EL RANGO DE ANGULOS CON UN IF
    if(((PI/4 > angle) ||(-PI/4 < angle)))
        return;
    uint8_t mangol =101 + (uint8_t)(40*angle+20*PI)/PI;
    TIM3->CCR2= mangol;
}

/*----- Configuration -----*/
void confRCC(void){
                /*    IOB,    IOA,   AF*/
    RCC->APB2ENR |= (1<<3)|(1<<2)|(1<<0); // GPIOA GPIOB

    RCC->APB1ENR |= (1<<0) | (1<<1); //TIM2 y TIM3
}
void confGPIO(void){

    GPIOA->CRL &= ~(0x0FFFF0FF);
    /*A0 A1 Outs OpenDrain MaxSpeed*/
    GPIOA->CRL |= (2<<6)|(3<<4)|(2<<2)|(3<<0);
    /*A3 A4 A5 A6 Output PushPull */
    GPIOA->CRL |= (3<<24)|(3<<20)|(3<<16)|(3<<12);
    // AF01 Se configuran

    //GPIOB
    GPIOB->CRL &= ~(0xF000FF);
    GPIOB->CRL |= (2<<22)|(3<<20)|(3<<4)|(3<<0);
    AFIO->MAPR |= (2<<10);
    //PB4 AF2 TIM3 CH1



}

void confTIMER(void)
{

    TIM2->PSC = 1;
                /* CH1      CH2*/
    TIM2->CCMR1 |=(6<<4)|(6<<12); // Enable PWM
    //TIM2->CCMR1 |=(1<<3)|(1<<11); // Preload
    TIM2->CCER  |=(1<<0) |(1<<4);//ENABLECHANEL1

    TIM2->ARR  =65535; /*8.2 mS*/

    TIM2->CCR1= 0;//DUTYCYCLE 50% CHANEL1
    TIM2->CCR2 =0;//pwm duty cycle 50% CHANEL 2
    TIM2->CR1 |= (1<<0);

	/*CH1    CH2*/

    TIM3->PSC = 99;
                /* CH1*/
    TIM3->CCMR1 |=(6<<12); // Enable PWM
    TIM3->CCER  |=(1<<4);//ENABLE CHANEL 2
    /*
    1.25 - 1.75 ms
    Servo
    2 ms 90
    1 ms -90

    20 ms  50hz PERIOD
    */
    TIM3->ARR  =1599; /*8k/50*/

    TIM3->CCR2= 120;//1600*1.5/20 => 120  7.5% 0°
    TIM3->CR1 |= (1<<0);

    /*
    Valor minimo 100 -45
    Valor maximo 140 +45
    */

}


void delay_ms(uint32_t delay){
	for(uint32_t i=0;i<delay;i++){
	for(uint32_t j=0;j<11500;j++);
	}
}


void config(void){
    confRCC();
    confGPIO();
    confTIMER();

}

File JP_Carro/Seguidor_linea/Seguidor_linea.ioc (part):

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Mcu.Name=STM32F411C(C-E)Ux
Mcu.Package=UFQFPN48
Mcu.UserName=STM32F411CEUx
PA0-WKUP.Signal=ADCx_IN0
PA1.Signal=ADCx_IN1
PA10.Signal=S_TIM1_CH3
PA2.GPIOParameters=GPIO_Label
PA2.GPIO_Label=AIN1
PA2.Signal=GPIO_Output
PA3.GPIOParameters=GPIO_Label
PA3.GPIO_Label=AIN2
PA3.Signal=GPIO_Output
PA4.GPIOParameters=GPIO_Label
PA4.GPIO_Label=BIN1
PA4.Signal=GPIO_Output
PA5.GPIOParameters=GPIO_Label
PA5.GPIO_Label=BIN2
PA5.Signal=GPIO_Output
PA8.Signal=S_TIM1_CH1
PA9.Signal=S_TIM1_CH2
PH0\ -\ OSC_IN.Mode=HSE-External-Oscillator
PH0\ -\ OSC_IN.Signal=RCC_OSC_IN
PH1\ -\ OSC_OUT.Mode=HSE-External-Oscillator
PH1\ -\ OSC_OUT.Signal=RCC_OSC_OUT
RCC.HSE_VALUE=25000000
RCC.SYSCLKFreq_VALUE=100000000
RCC.SYSCLKSource=RCC_SYSCLKSOURCE_PLLCLK
board=custom

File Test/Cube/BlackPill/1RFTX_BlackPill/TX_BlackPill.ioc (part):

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Mcu.Name=STM32F411C(C-E)Ux
Mcu.Package=UFQFPN48
Mcu.UserName=STM32F411CEUx
PA0-WKUP.Signal=ADCx_IN0
PA10.GPIOParameters=GPIO_Label,GPIO_ModeDefaultEXTI
PA10.GPIO_Label=IRQ
PA10.GPIO_ModeDefaultEXTI=GPIO_MODE_IT_FALLING
PA10.Signal=GPXTI10
PA5.Mode=Full_Duplex_Master
PA5.Signal=SPI1_SCK
PA6.Mode=Full_Duplex_Master
PA6.Signal=SPI1_MISO
PA7.Mode=Full_Duplex_Master
PA7.Signal=SPI1_MOSI
PA8.GPIOParameters=GPIO_Speed,GPIO_Label
PA8.GPIO_Label=CSN
PA8.GPIO_Speed=GPIO_SPEED_FREQ_VERY_HIGH
PA8.Signal=GPIO_Output
PA9.GPIOParameters=GPIO_Speed,GPIO_Label
PA9.GPIO_Label=CE
PA9.GPIO_Speed=GPIO_SPEED_FREQ_VERY_HIGH
PA9.Signal=GPIO_Output
PB12.GPIOParameters=GPIO_PuPd
PB12.GPIO_PuPd=GPIO_PULLDOWN
PB12.Signal=GPIO_Input
PB13.GPIOParameters=GPIO_PuPd
PB13.GPIO_PuPd=GPIO_PULLDOWN
PB13.Signal=GPIO_Input
PB14.GPIOParameters=GPIO_PuPd
PB14.GPIO_PuPd=GPIO_PULLDOWN
PB14.Signal=GPIO_Input
PB8.Mode=I2C
PB8.Signal=I2C1_SCL
PB9.Mode=I2C
PB9.Signal=I2C1_SDA
RCC.HSE_VALUE=25000000
RCC.SYSCLKFreq_VALUE=72000000
RCC.SYSCLKSource=RCC_SYSCLKSOURCE_PLLCLK
board=custom

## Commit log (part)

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2025-12-18 created repo
2025-12-19 Tested NRF24L01 not working, could be the voltage source'
2025-12-20 Added tx
2025-12-21 Add tst with STM32
2025-12-28 RFTX_BlackPill working
2025-12-28 RFRX BluePill working
2025-12-28 Working comm between black n blue pill w/ RF Struct
2025-12-28 Servo didnt work in the RFCar
2025-12-31 Fixed Servomotor on RF Car, (didnt considered the PLL)
2025-12-31 Added MPU6050 to TX BlackPill
2026-01-04 Changed RFCAR->CarritoBLPRX
2026-01-04 Ported the TX code to BluePill
2026-01-04 Implemented speed and direction, pending to test on RX
2026-02-01 Working Hand
2026-02-02 Working Car and Hand pending HW
2026-02-23 Se añade sistema minimo de hardware
2026-02-23 Se añadió Esquemas preliminares del carro
2026-02-24 puse una nueva libreria
2026-02-24 Añadi nuevo proyecto del puente-H
2026-02-24 Driver test Finalizado
2026-02-25 Carrito pcb, 25-02-26
2026-02-26 Carrito 26-02-26
2026-02-26 added an advance for the CAR PCB
2026-02-27 Placa de carro terminada al menos preliminarmente
2026-02-28 Modified La Mano & Added Xtal Footprint
2026-03-01 Actualizacion minima de repo
2026-03-01 Añadido divisor de tension para bateria, y conectir para luces indicadoras de bateria
2026-03-01 Cambios en la posicion d elas luces en el codigo
2026-03-12 PCBCAR FULL
2026-03-12 HAND FULL
2026-03-13 Rearranged components
2026-03-13 Added PowerPlane
2026-03-29 Modified Placa Mano
2026-04-01 Pending to add MPU6050 Footprint
2026-04-02 Añadidos hoyos placa carro
2026-04-07 4-7-26
2026-04-07 Updated Kicad
2026-04-07 Pending to route voltage tracks
2026-04-07 Small Joshua Changes
2026-04-08 Pending to route voltages, expected to do one side
2026-04-08 Correción menor
2026-05-05 Correxiones minimas
2026-05-07 Added bottom layer, pending to aprove
2026-05-16 Increased the vein sizes
2026-06-05 El chingao proyecto de jp
2026-06-05 Added Membership Functions
2026-06-05 Fixed Low and High Trapezoidal on FuzzyLogic
2026-06-06 Fuzzy_logic.c Fuzzy_logic.h agregados
2026-06-07 Datos del figma agregados
2026-06-07 Funciones low, mid, mid2,high agregadas
2026-06-07 Correciones
2026-06-09 Centroide y otras cosas
2026-06-09 Ya compilo
2026-06-09 aversi
2026-06-10 Falta fuzificacion
2026-06-10 Created Schematic
2026-06-10 Placa terminada
2026-06-11 PCB full
2026-06-11 IMplementacion main
2026-06-11 Cambio de reglas Mm
2026-06-12 Que so
2026-06-12 Centroide Arreglado
2026-06-12 Centroide Arreglado ahora si -- 2
2026-06-12 Parece que jala
2026-06-13 Added Readme
2026-06-17 Cambiamos orden trapecios y se arreglo
2026-06-17 Fixed Car
2026-06-17 Added Documentation
2026-06-20 Readme 1
2026-06-20 Modify prototype image in readme.md
    Updated image source for the prototype and added a placeholder image.
2026-06-20 Readme casifinal
2026-06-20 Readme 2
2026-06-23 Kicad 9.0->10.0
2026-06-23 DRC 0 Errors (Board cleareance errors, Fix: Increased Board size) Fixed mismatch size on 2 gnd tracks
2026-06-23 Fixed Readme
2026-06-29 6-29 Added Potentiometer Added Voltage divider for Battery Sensor Changed Layer tracks of NRF24
2026-06-29 Updated LogFile
2026-06-29 6-29 DRC Check Connect Resistor on PB2
2026-06-29 6-29 Fixed MPU orientation Added Vias
